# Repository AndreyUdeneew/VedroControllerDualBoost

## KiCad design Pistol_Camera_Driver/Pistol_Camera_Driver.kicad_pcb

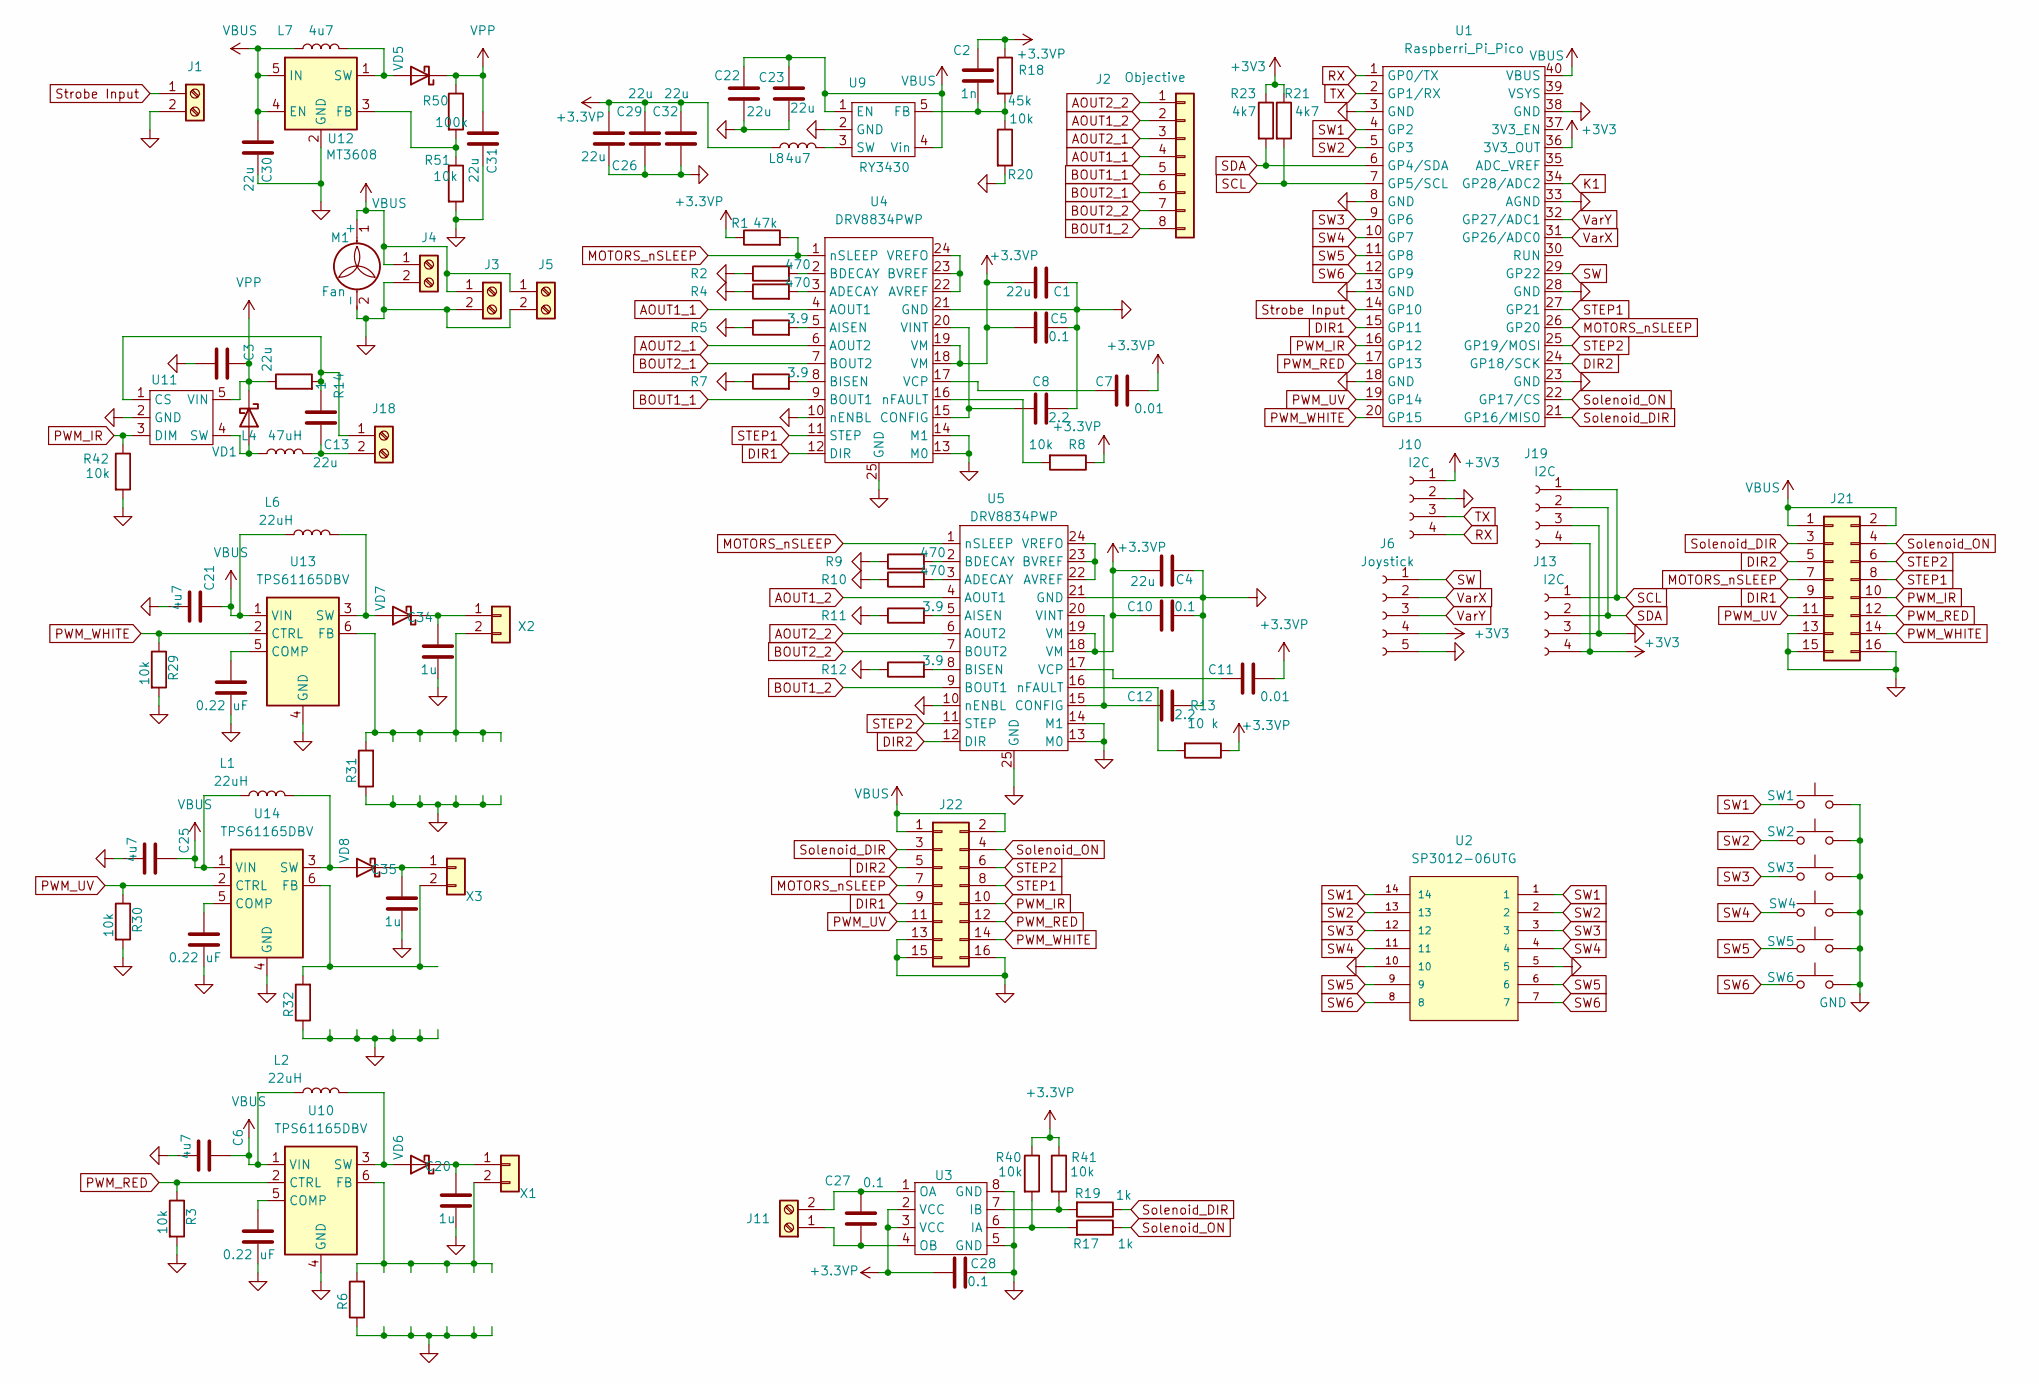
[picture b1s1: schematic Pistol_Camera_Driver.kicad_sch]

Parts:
C1, C3, C4, C13, C22, C23, C26, C29, C32: 22u; C_0805_2012Metric_Pad1.18x1.45mm_HandSolder
C2: 1n; C_0603_1608Metric_Pad1.08x0.95mm_HandSolder
C5, C10, C27, C28: 0.1; C_0603_1608Metric_Pad1.08x0.95mm_HandSolder
C6, C21, C25: 4u7; C_0805_2012Metric_Pad1.18x1.45mm_HandSolder
C7, C11: 0.01; C_0603_1608Metric_Pad1.08x0.95mm_HandSolder
C8, C12: 2.2; C_0603_1608Metric_Pad1.08x0.95mm_HandSolder
C9, C24, C33: 0.22 uF; C_0603_1608Metric_Pad1.08x0.95mm_HandSolder
C20, C34, C35: 1u; C_0603_1608Metric_Pad1.08x0.95mm_HandSolder
C30, C31: 22u; C_0603_1608Metric_Pad1.08x0.95mm_HandSolder
J1, J3, J4, J5, J18: Screw_Terminal_01x02; JST_XH_B2B-XH-A_1x02_P2.50mm_Vertical
J2: Objective; PinSocket_1x08_P1.27mm_Vertical
J6: Joystick; JST_XH_B5B-XH-A_1x05_P2.50mm_Vertical
J10: I2C; PinSocket_1x04_P2.54mm_Vertical
J11: Screw_Terminal_01x02; PinSocket_1x02_P1.27mm_Vertical
J13, J19: I2C; JST_XH_B4B-XH-A_1x04_P2.50mm_Vertical
J21, J22: Conn_02x08_Odd_Even; IDC-Header_2x08_P2.54mm_Vertical
L1, L2, L6: 22uH; L_APV_ANR6045
L4: 47uH; L_APV_ANR5045
L7, L8: 4u7; L_Chilisin_BMRx00040412
M1: Fan
R1: 47k; R_0603_1608Metric_Pad0.98x0.95mm_HandSolder
R2, R4, R9, R10: 470; R_0603_1608Metric_Pad0.98x0.95mm_HandSolder
R3, R8, R20, R29, R30, R40, R41, R42, R51: 10k; R_0603_1608Metric_Pad0.98x0.95mm_HandSolder
R5, R7, R11, R12: 3.9; R_0603_1608Metric_Pad0.98x0.95mm_HandSolder
R6, R31, R32: 1 Ohm; R_0603_1608Metric_Pad0.98x0.95mm_HandSolder
R13: 10 k; R_0603_1608Metric_Pad0.98x0.95mm_HandSolder
R14: 1; R_0603_1608Metric_Pad0.98x0.95mm_HandSolder
R17, R19: 1k; R_0603_1608Metric_Pad0.98x0.95mm_HandSolder
R18: 45k; R_0603_1608Metric_Pad0.98x0.95mm_HandSolder
R21, R23: 4k7; R_0603_1608Metric_Pad0.98x0.95mm_HandSolder
R50: 100k; R_0603_1608Metric_Pad0.98x0.95mm_HandSolder
SW1, SW2, SW3, SW4, SW5, SW6: SW_Push; SW_PUSH_6mm
U1: Raspberri_Pi_Pico; RP2040-LCD-0.96
U2: SP3012-06UTG; DFN-14_1.35x3.5mm_P0.5mm; PARTREV 02/23/17
U3: SOIC-8_3.9x4.9mm_P1.27mm
U4, U5: DRV8834PWP
U9: RY3430; SOT-23-5
U10, U13, U14: TPS61165DBV; SOT-23-6
U11: SOT-89-5
U12: MT3608; SOT-23-6
VD1, VD5, VD6, VD7, VD8: CDBA3100-HF; D_SOD-123
X1, X2, X3: Conn_01x02; JST_XH_B2B-XH-A_1x02_P2.50mm_Vertical

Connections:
+3.3VP: C1.1, C2.1, C4.1, C5.2, C7.2, C10.1, C11.2, C26.1, C28.2, C29.2, C32.2, L8.1, R1.1, R8.1, R13.1, R18.1, R40.1, R41.1, U3.2 (VCC), U3.3 (VCC), U4.18 (VM), U4.19 (VM), U5.18 (VM), U5.19 (VM)
+3V3: J6.4, J10.1, J13.4, J19.4, R21.1, R23.1, U1.36 (3V3_OUT)
AOUT1_1: J2.4, U4.4 (AOUT1)
AOUT1_2: J2.2, U5.4 (AOUT1)
AOUT2_1: J2.3, U4.6 (AOUT2)
AOUT2_2: J2.1, U5.6 (AOUT2)
BOUT1_1: J2.5, U4.9 (BOUT1)
BOUT1_2: J2.8, U5.9 (BOUT1)
BOUT2_1: J2.6, U4.7 (BOUT2)
BOUT2_2: J2.7, U5.7 (BOUT2)
DIR1: J21.9, J22.9, U1.15 (GP11), U4.12 (DIR)
DIR2: J21.5, J22.5, U1.24 (GP18/SCK), U5.12 (DIR)
GND: C1.2, C3.1, C4.2, C5.1, C6.2, C8.2, C9.2, C10.2, C12.2, C20.2, C21.2, C22.2, C23.1, C24.2, C25.2, C26.2, C28.1, C29.1, C30.2, C31.2, C32.1, C33.2, C34.2, C35.2, J1.2, J3.2, J4.2, J5.2, J6.5, J10.2, J13.3, J19.3, J21.13, J21.15, J21.16, J22.13, J22.15, J22.16, M1.2 (-), R2.1, R3.2, R4.1, R5.1, R6.1, R7.1, R9.1, R10.1, R11.1, R12.1, R20.2, R29.2, R30.2, R31.1, R32.1, R42.2, R51.2, SW1.2, SW2.2, SW3.2, SW4.2, SW5.2, SW6.2, U1.3 (GND), U1.8 (GND), U1.13 (GND), U1.18 (GND), U1.23 (GND), U1.28 (GND), U1.33 (AGND), U1.38 (GND), U2.5, U2.10, U3.5 (GND), U3.8 (GND), U4.10 (nENBL), U4.13 (M0), U4.14 (M1), U4.21 (GND), U4.25 (GND), U5.10 (nENBL), U5.13 (M0), U5.14 (M1), U5.21 (GND), U5.25 (GND), U9.2 (GND), U10.4 (GND), U11.2 (GND), U12.2 (GND), U13.4 (GND), U14.4 (GND)
K1: U1.34 (GP28/ADC2)
MOTORS_nSLEEP: J21.7, J22.7, R1.2, U1.26 (GP20), U4.1 (nSLEEP), U5.1 (nSLEEP)
unnamed: C27.2, J11.1, U3.4 (OB)
unnamed: C27.1, J11.2, U3.1 (OA)
unnamed: C13.1, J18.1, R14.2, U11.1 (CS)
unnamed: C13.2, J18.2, L4.2
unnamed: R17.2, R40.2, U3.6 (IA)
unnamed: R19.2, R41.2, U3.7 (IB)
unnamed: R4.2, U4.3 (ADECAY)
unnamed: R5.2, U4.5 (AISEN)
unnamed: U4.22 (AVREF), U4.23 (BVREF), U4.24 (VREFO)
unnamed: R2.2, U4.2 (BDECAY)
unnamed: R7.2, U4.8 (BISEN)
unnamed: C8.1, U4.15 (CONFIG), U4.20 (VINT)
unnamed: C7.1, U4.17 (VCP)
unnamed: R8.2, U4.16 (nFAULT)
unnamed: R10.2, U5.3 (ADECAY)
unnamed: R11.2, U5.5 (AISEN)
unnamed: U5.22 (AVREF), U5.23 (BVREF), U5.24 (VREFO)
unnamed: R9.2, U5.2 (BDECAY)
unnamed: R12.2, U5.8 (BISEN)
unnamed: C12.1, U5.15 (CONFIG), U5.20 (VINT)
unnamed: C11.1, U5.17 (VCP)
unnamed: R13.2, U5.16 (nFAULT)
unnamed: C2.2, R18.2, R20.1, U9.5 (FB)
unnamed: L8.2, U9.3 (SW)
unnamed: C9.1, U10.5 (COMP)
unnamed: R6.2, U10.6 (FB), X1.2
unnamed: L2.2, U10.3 (SW), VD6.2 (A)
unnamed: L4.1, U11.4 (SW), VD1.2 (A)
unnamed: R50.2, R51.1, U12.3 (FB)
unnamed: L7.2, U12.1 (SW), VD5.2 (A)
unnamed: C24.1, U13.5 (COMP)
unnamed: R31.2, U13.6 (FB), X2.2
unnamed: L6.2, U13.3 (SW), VD7.2 (A)
unnamed: C33.1, U14.5 (COMP)
unnamed: R32.2, U14.6 (FB), X3.2
unnamed: L1.2, U14.3 (SW), VD8.2 (A)
unnamed: C20.1, VD6.1 (K), X1.1
unnamed: C34.1, VD7.1 (K), X2.1
unnamed: C35.1, VD8.1 (K), X3.1
PWM_IR: J21.10, J22.10, R42.1, U1.16 (GP12), U11.3 (DIM)
PWM_RED: J21.12, J22.12, R3.1, U1.17 (GP13), U10.2 (CTRL)
PWM_UV: J21.11, J22.11, R30.1, U1.19 (GP14), U14.2 (CTRL)
PWM_WHITE: J21.14, J22.14, R29.1, U1.20 (GP15), U13.2 (CTRL)
RX: J10.4, U1.1 (GP0/TX)
SCL: J13.1, J19.1, R21.2, U1.7 (GP5/SCL)
SDA: J13.2, J19.2, R23.2, U1.6 (GP4/SDA)
STEP1: J21.8, J22.8, U1.27 (GP21), U4.11 (STEP)
STEP2: J21.6, J22.6, U1.25 (GP19/MOSI), U5.11 (STEP)
SW: J6.1, U1.29 (GP22)
SW1: SW1.1, U1.4 (GP2), U2.1, U2.14
SW2: SW2.1, U1.5 (GP3), U2.2, U2.13
SW3: SW3.1, U1.9 (GP6), U2.3, U2.12
SW4: SW4.1, U1.10 (GP7), U2.4, U2.11
SW5: SW5.1, U1.11 (GP8), U2.6, U2.9
SW6: SW6.1, U1.12 (GP9), U2.7, U2.8
Solenoid_DIR: J21.3, J22.3, R19.1, U1.21 (GP16/MISO)
Solenoid_ON: J21.4, J22.4, R17.1, U1.22 (GP17/CS)
Strobe Input: J1.1, U1.14 (GP10)
TX: J10.3, U1.2 (GP1/RX)
VBUS: C6.1, C21.1, C22.1, C23.2, C25.1, C30.1, J3.1, J4.1, J5.1, J21.1, J21.2, J22.1, J22.2, L1.1, L2.1, L6.1, L7.1, M1.1 (+), U1.40 (VBUS), U9.1 (EN), U9.4 (Vin), U10.1 (VIN), U12.4 (EN), U12.5 (IN), U13.1 (VIN), U14.1 (VIN)
VPP: C3.2, C31.1, R14.1, R50.1, U11.5 (VIN), VD1.1 (K), VD5.1 (K)
VarX: J6.2, U1.31 (GP26/ADC0)
VarY: J6.3, U1.32 (GP27/ADC1)

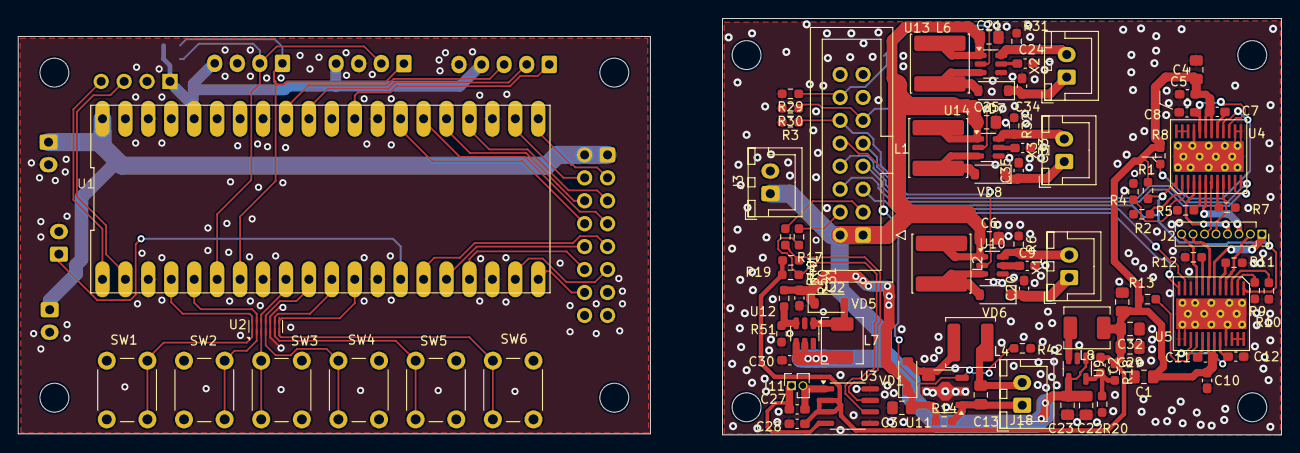
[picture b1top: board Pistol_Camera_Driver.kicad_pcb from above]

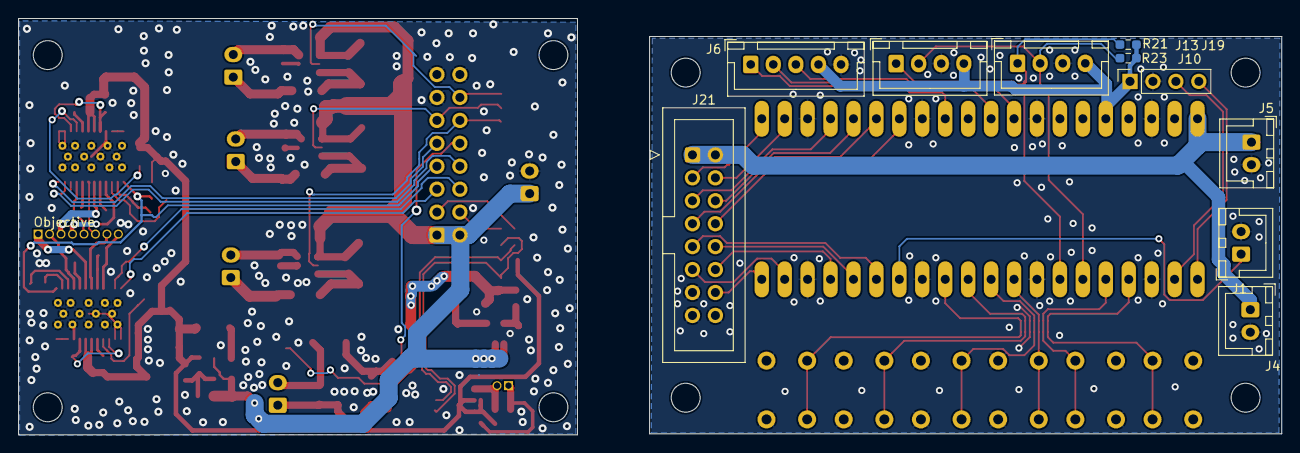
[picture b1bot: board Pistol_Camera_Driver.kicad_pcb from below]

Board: 2 copper layers, 61.9 x 46.1 mm, 102 parts (10 on the bottom side), 77 nets.

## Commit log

2025-02-17 v0.1 draft routing
